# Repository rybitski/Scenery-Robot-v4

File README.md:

# SceneryRobotV4
Version 4 of the UVA Stage Robotics Development Project

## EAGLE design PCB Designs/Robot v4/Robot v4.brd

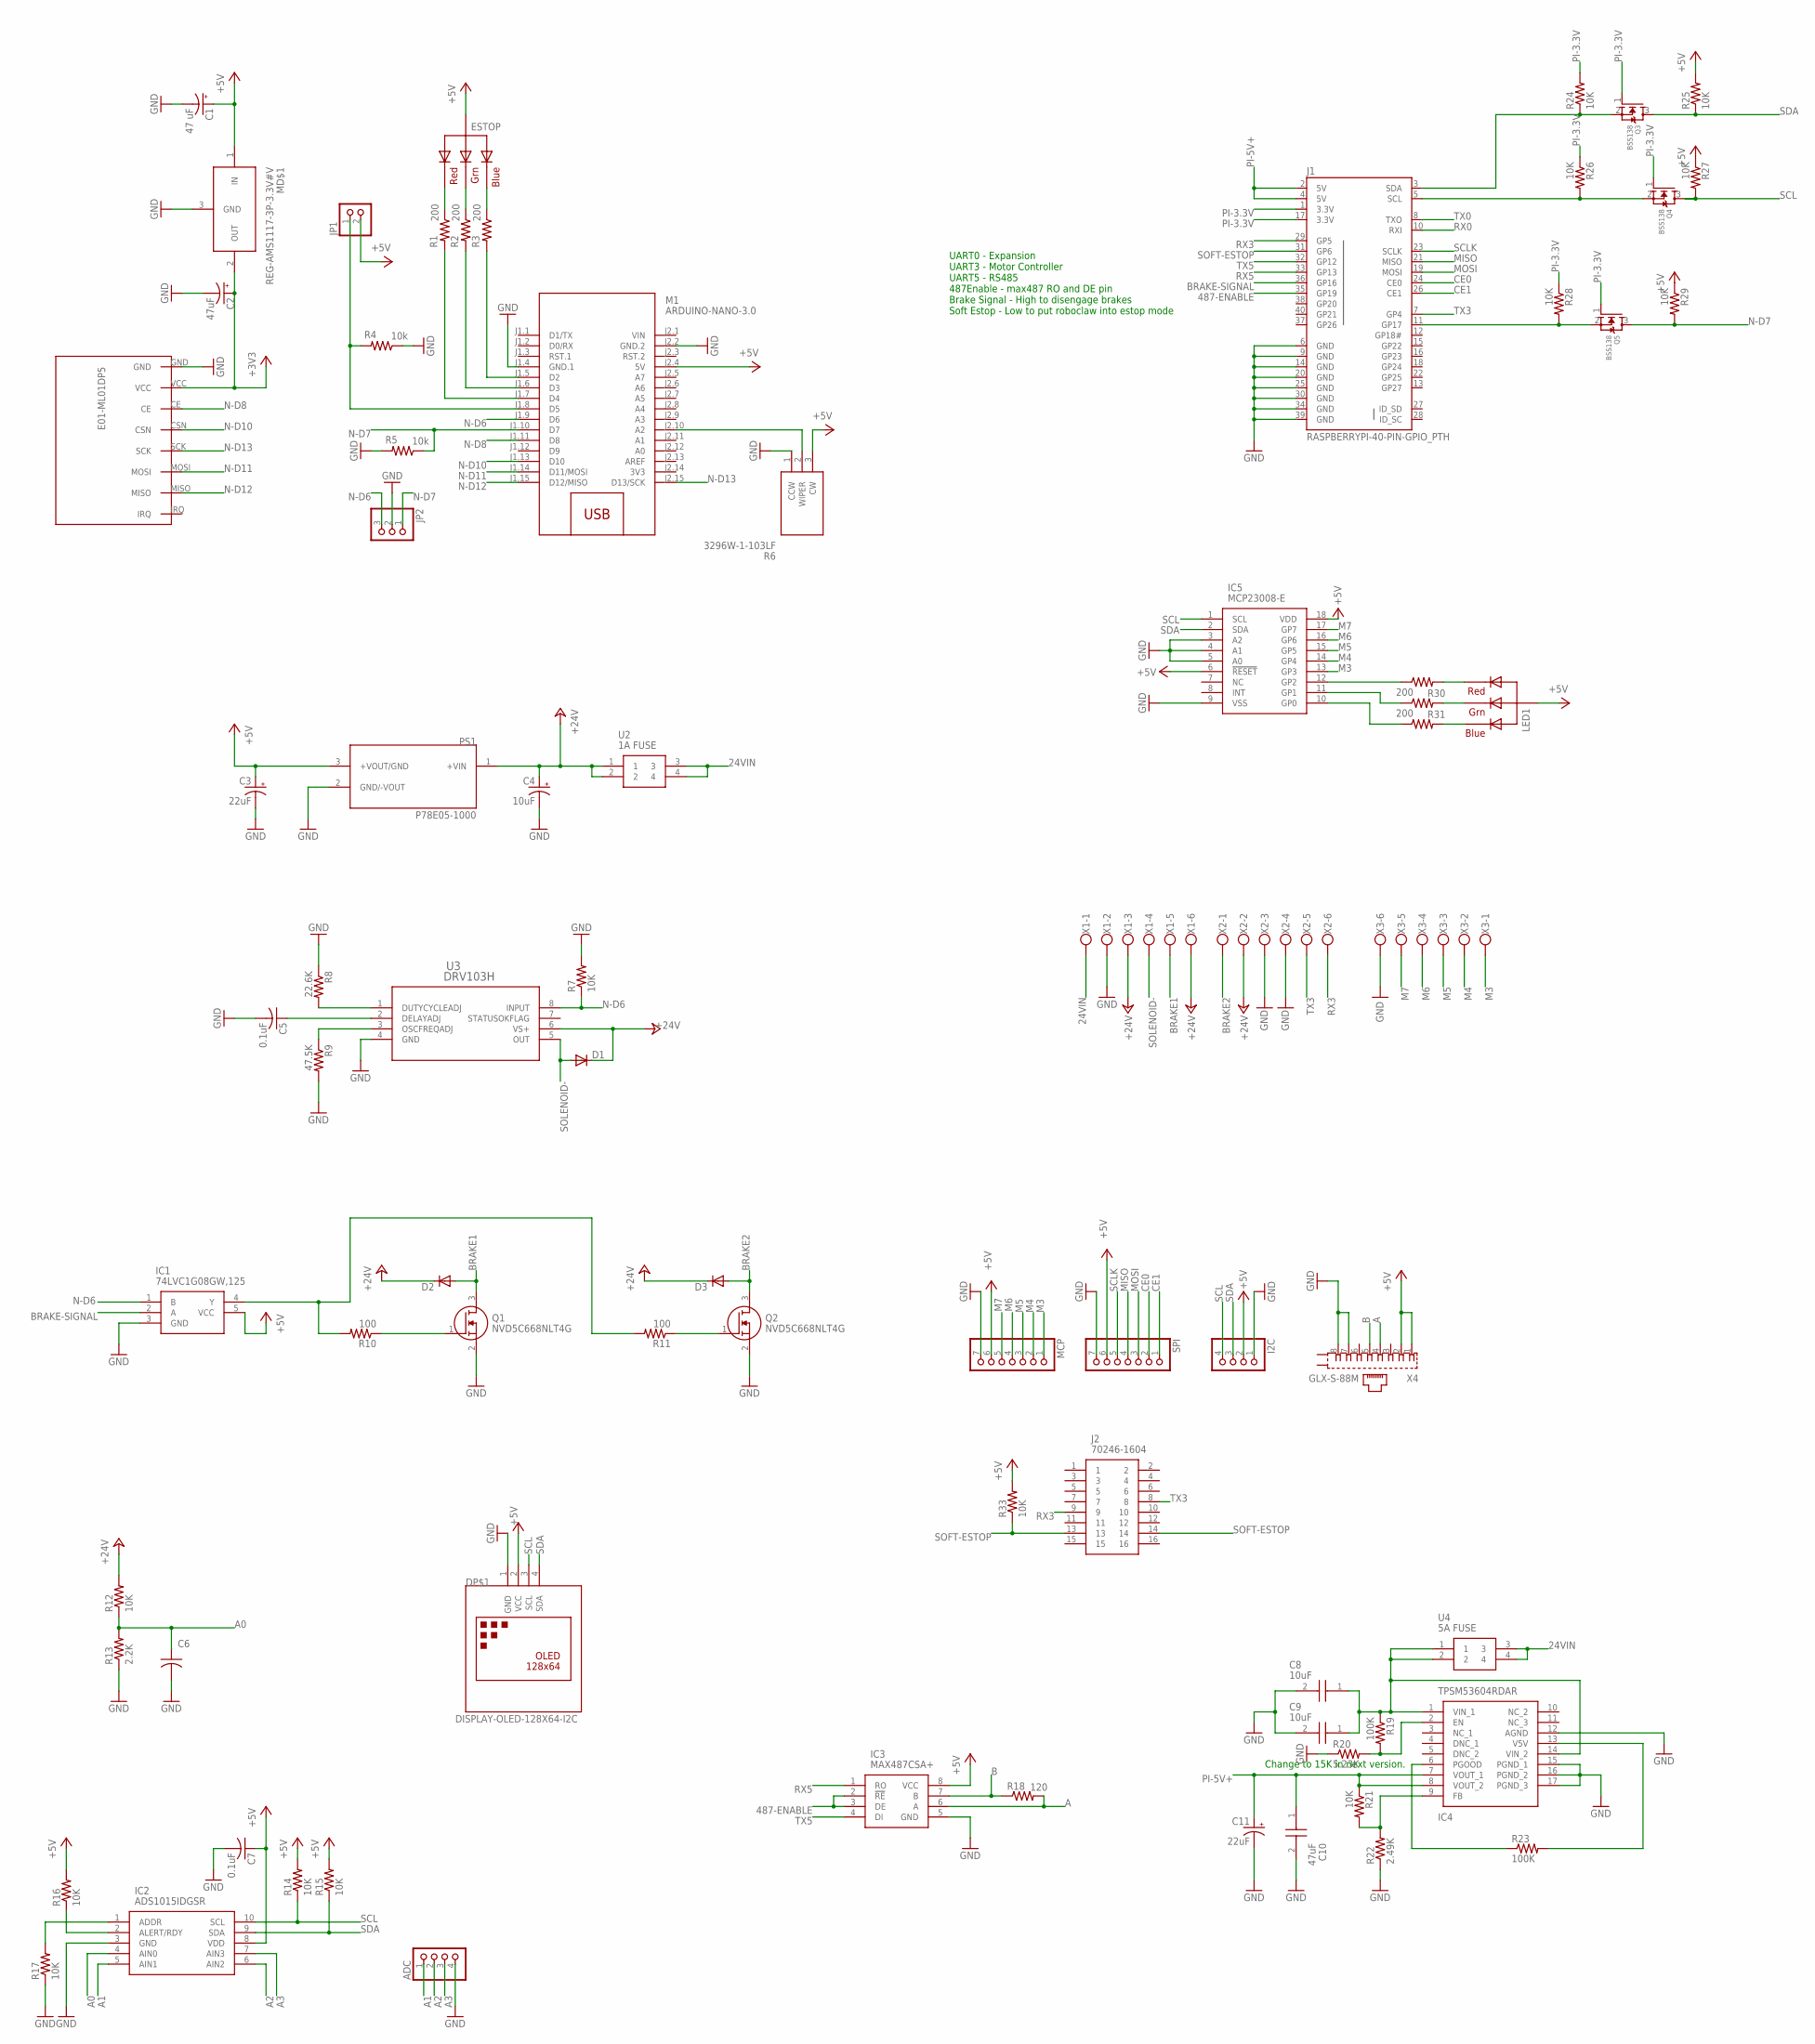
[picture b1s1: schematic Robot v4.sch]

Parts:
ADC: PINHD-1X4; 1X04
C1: 47 uF; E2,5-5
C2: 47uF; E2,5-5
C3, C11: 22uF; E3,5-8
C4: 10uF; E3,5-8
C5, C7: 0.1uF; C0805
C6: 0.01uF; C0805
C8, C9: 10uF; CAPC3216X180N
C10: 47uF; CAPC2012X145N
D1, D2, D3: DIODESOD-123; SOD-123
DP$1: DISPLAY-OLED-128X64-I2C
ESTOP: RGBLED_CA-5MM; LED5MMRGB
I2C: PINHD-1X4; 1X04
IC1: 74LVC1G08GW,125; SOT65P212X110-5N
IC2: ADS1015IDGSR; SOP50P490X110-10N
IC3: MAX487CSA+; SOIC127P600X175-8N
IC4: TPSM53604RDAR
IC5: MCP23008-E; SOIC127P1030X265-18N
J1: RASPBERRYPI-40-PIN-GPIO_PTH; 2X20_SHROUDED
J2: 70246-1604; SHDR16W64P254_2X8_2794X889X947
JP1: PINHD-1X2; 1X02
JP2: PINHD-1X3; 1X03
LED1: RGBLED_CA-5MM; LED5MMRGB
M1: ARDUINO-NANO-3.0
MCP: PINHD-1X7; 1X07
MD$1: REG-AMS1117-3P-3.3V#V; REG-AMS1117-3P#V
MD$2: E01-ML01DP5
PS1: P78E05-1000; CONV_P78E05-1000
Q1, Q2: NVD5C668NLT4G; DPAK_(SINGLE-GAUGE)_TO-252(369
Q3, Q4, Q5: BSS138; SOT23
R1, R2, R3, R30, R31, R32: 200; M0805
R4, R5: 10k; M0805
R6: 3296W-1-103LF; SHDR3W54P0X254_1X3_953X483X115
R7, R12: 10K; M0805
R8: 22.6K; M0805
R9: 47.5K; M0805
R10, R11: 100; M0805
R13: 2.2K; M0805
R14, R15, R16, R17, R21, R24, R25, R26, R27, R28, R29, R33: 10K; R0805
R18: 120; R0805
R19, R23: 100K; R0805
R20: 5.23K; R0805
R22: 2.49K; R0805
SPI: PINHD-1X7; 1X07
U2: 1A FUSE; 3568
U3: DRV103H; DDA8
U4: 5A FUSE; 3568
X1, X2, X3: W237-136
X4: GLX-S-88M

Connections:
3V3: M1.J2.14 (3V3)
24VIN: U2.3, U2.4, U4.3, U4.4, X1.1
487-ENABLE: IC3.2 (!RE), IC3.3 (DE), J1.35 (GP19)
+3V3: C2.+, MD$1.2 (OUT), MD$2.VCC
+5V: C1.+, C3.+, C7.1, DP$1.2 (VCC), ESTOP.2 (VCC), I2C.2, IC1.5 (VCC), IC2.8 (VDD), IC3.8 (VCC), IC5.6 (!RESET), IC5.18 (VDD), JP1.2, LED1.2 (VCC), M1.J2.4 (5V), MCP.6, MD$1.1 (IN), PS1.3 (+VOUT/GND), R6.3 (CW), R14.2, R15.2, R16.2, R25.2, R27.1, R29.1, R33.2, SPI.6, X4.1, X4.2
+24V: C4.+, D1.C, D2.C, D3.C, PS1.1 (+VIN), R12.2, U2.1, U2.2, U3.6 (VS+), X1.3, X1.6, X2.2
A: IC3.6 (A), R18.2, X4.4
A0: C6.1, IC2.4 (AIN0), R12.1, R13.2
A1: ADC.1, IC2.5 (AIN1)
A2: ADC.2, IC2.6 (AIN2)
A3: ADC.3, IC2.7 (AIN3)
B: IC3.7 (B), R18.1, X4.5
BRAKE1: D2.A, Q1.3 (D), X1.5
BRAKE2: D3.A, Q2.3 (D), X2.1
BRAKE-SIGNAL: IC1.2 (A), J1.36 (GP16)
CE0: J1.24 (CE0), SPI.2
CE1: J1.26 (CE1), SPI.1
GND: ADC.4, C1.-, C2.-, C3.-, C4.-, C5.2, C6.2, C7.2, C8.2, C9.2, C10.2, C11.-, DP$1.1 (GND), I2C.1, IC1.3 (GND), IC2.3 (GND), IC3.5 (GND), IC4.12 (AGND), IC4.15 (PGND_1), IC4.16 (PGND_2), IC4.17 (PGND_3), IC5.3 (A2), IC5.4 (A1), IC5.5 (A0), IC5.9 (VSS), J1.6 (GND), J1.9 (GND), J1.14 (GND), J1.20 (GND), J1.25 (GND), J1.30 (GND), J1.34 (GND), J1.39 (GND), JP2.2, M1.J1.4 (GND.1), M1.J2.2 (GND.2), MCP.7, MD$1.3 (GND), MD$2.GND, PS1.2 (GND/-VOUT), Q1.2 (S), Q2.2 (S), R4.1, R5.2, R6.1 (CCW), R7.2, R8.1, R9.2, R13.1, R17.1, R20.1, R22.1, SPI.7, U3.4 (GND), X1.2, X2.3, X2.4, X3.6, X4.7, X4.8
M3: IC5.13 (GP3), MCP.1, X3.1
M4: IC5.14 (GP4), MCP.2, X3.2
M5: IC5.15 (GP5), MCP.3, X3.3
M6: IC5.16 (GP6), MCP.4, X3.4
M7: IC5.17 (GP7), MCP.5, X3.5
MISO: J1.21 (MISO), SPI.4
MOSI: J1.19 (MOSI), SPI.3
unnamed: IC5.12 (GP2), R30.1
unnamed: IC5.11 (GP1), R31.1
unnamed: C8.1, C9.1, IC4.1 (VIN_1), IC4.14 (VIN_2), R19.1, U4.1, U4.2
unnamed: IC1.4 (Y), R10.2, R11.2
unnamed: J1.5 (SCL), Q4.2 (S), R26.2
unnamed: Q2.1 (G), R11.1
unnamed: Q1.1 (G), R10.1
unnamed: J1.3 (SDA), Q3.2 (S), R24.1
unnamed: IC5.10 (GP0), R32.1
unnamed: IC4.2 (EN), R19.2, R20.2
unnamed: IC4.9 (FB), R21.2, R22.2
unnamed: J1.11 (GP17), Q5.2 (S), R28.2
unnamed: IC4.13 (V5V), R23.2
unnamed: IC4.6 (PGOOD), R23.1
unnamed: IC2.2 (ALERT/RDY), R16.1
unnamed: IC2.1 (ADDR), R17.2
unnamed: LED1.1 (RED), R30.2
unnamed: LED1.3 (GREEN), R31.2
unnamed: LED1.4 (BLUE), R32.2
unnamed: ESTOP.4 (BLUE), R3.1
unnamed: ESTOP.3 (GREEN), R2.1
unnamed: ESTOP.1 (RED), R1.1
unnamed: M1.J1.5 (D2), R3.2
unnamed: JP1.1, M1.J1.8 (D5), R4.2
unnamed: M1.J1.6 (D3), R2.2
unnamed: M1.J1.7 (D4), R1.2
unnamed: M1.J2.10 (A2), R6.2 (WIPER)
unnamed: C5.1, U3.2 (DELAYADJ)
unnamed: R9.1, U3.3 (OSCFREQADJ)
unnamed: R8.2, U3.1 (DUTYCYCLEADJ)
N-D6: IC1.1 (B), JP2.3, M1.J1.9 (D6), R7.1, U3.8 (INPUT)
N-D7: JP2.1, M1.J1.10 (D7), Q5.3 (D), R5.1, R29.2
N-D8: M1.J1.11 (D8), MD$2.CE
N-D10: M1.J1.13 (D10), MD$2.CSN
N-D11: M1.J1.14 (D11/MOSI), MD$2.MOSI
N-D12: M1.J1.15 (D12/MISO), MD$2.MISO
N-D13: M1.J2.15 (D13/SCK), MD$2.SCK
PI-3.3V: J1.1 (3.3V), J1.17 (3.3V), Q3.1 (G), Q4.1 (G), Q5.1 (G), R24.2, R26.1, R28.1
PI-5V+: C10.1, C11.+, IC4.7 (VOUT_1), IC4.8 (VOUT_2), J1.2 (5V), J1.4 (5V), R21.1
RX0: J1.10 (RXI)
RX3: J1.29 (GP5), J2.9, X2.6
RX5: IC3.1 (RO), J1.33 (GP13)
SCL: DP$1.3 (SCL), I2C.4, IC2.10 (SCL), IC5.1 (SCL), Q4.3 (D), R14.1, R27.2
SCLK: J1.23 (SCLK), SPI.5
SDA: DP$1.4 (SDA), I2C.3, IC2.9 (SDA), IC5.2 (SDA), Q3.3 (D), R15.1, R25.1
SOFT-ESTOP: J1.31 (GP6), J2.13, J2.14, R33.1
SOLENOID-: D1.A, U3.5 (OUT), X1.4
TX0: J1.8 (TXO)
TX3: J1.7 (GP4), J2.8, X2.5
TX5: IC3.4 (DI), J1.32 (GP12)
VIN: M1.J2.1 (VIN)

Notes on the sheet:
UART0 - Expansion UART3 - Motor Controller UART5 - RS485 487Enable - max487 RO and DE pin Brake Signal - High to disengage brakes Soft Estop - Low to put roboclaw into estop mode
Change to 15K in next version.

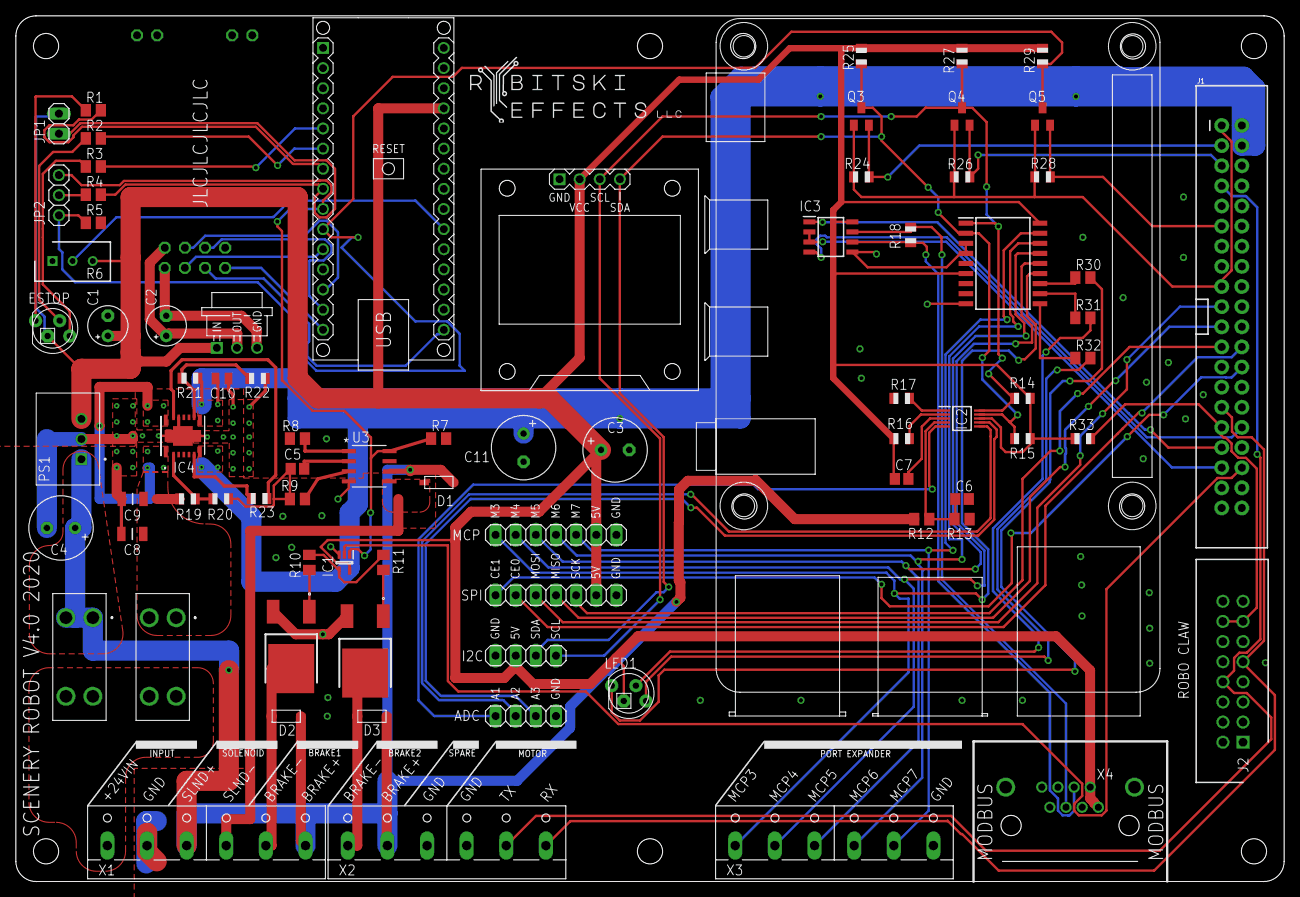
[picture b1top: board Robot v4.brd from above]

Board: 2 copper layers, 160.0 x 109.2 mm, 79 parts (0 on the bottom side), 72 nets.

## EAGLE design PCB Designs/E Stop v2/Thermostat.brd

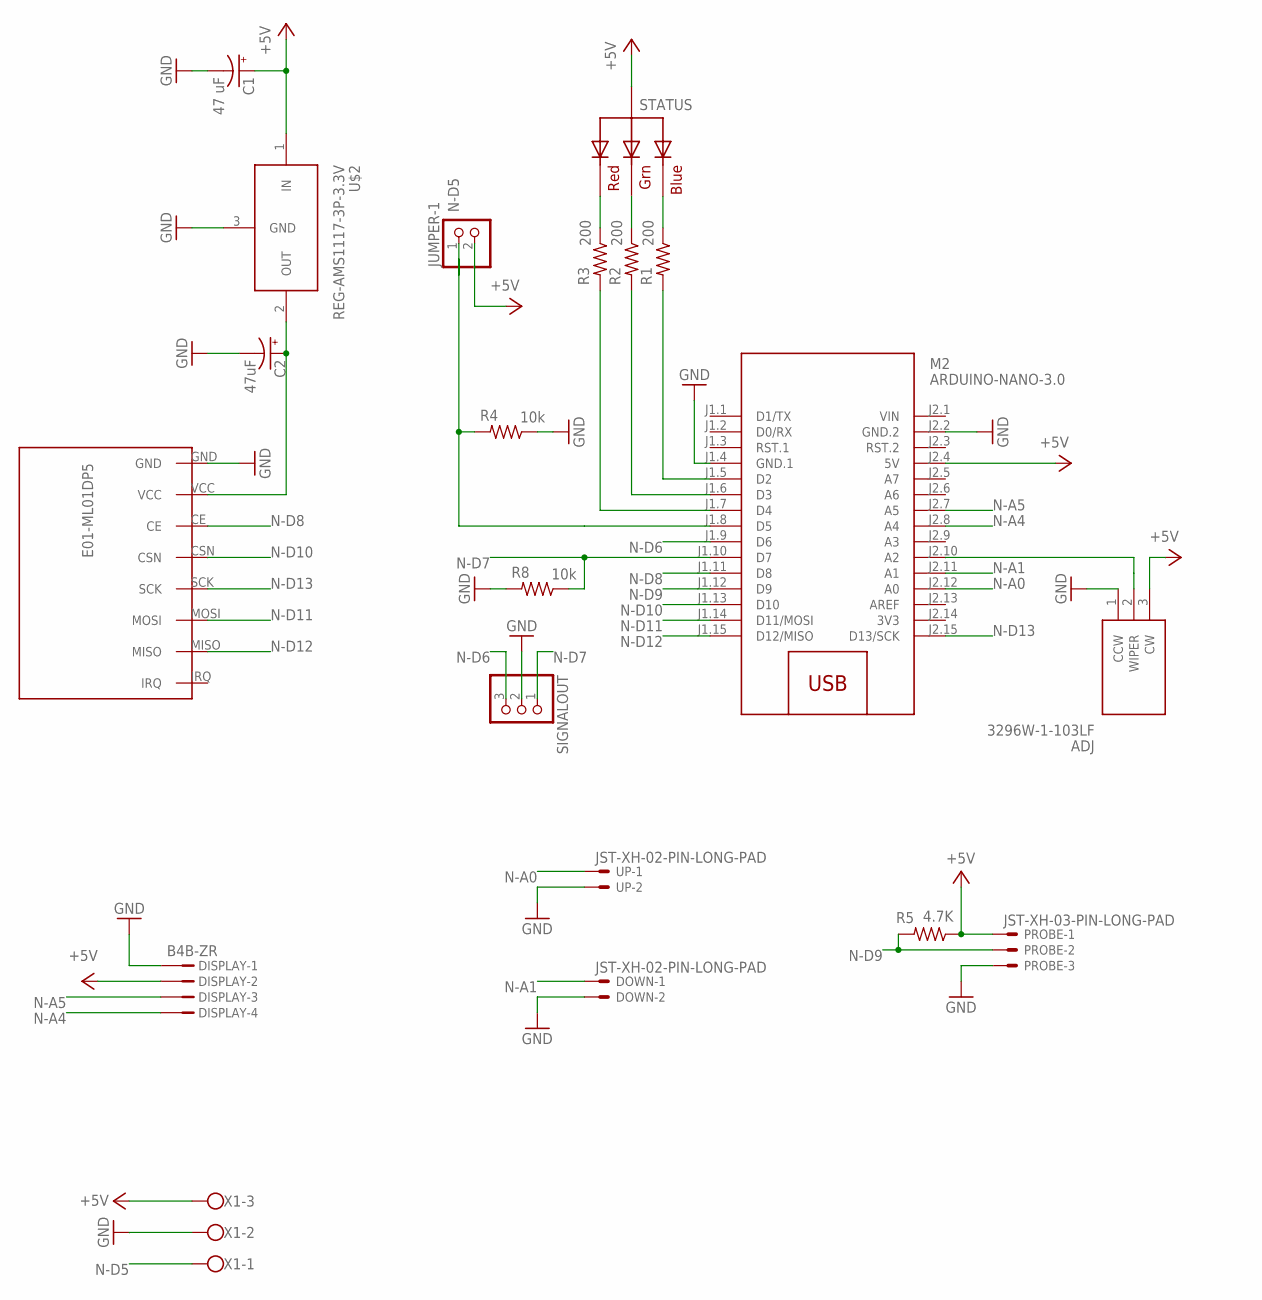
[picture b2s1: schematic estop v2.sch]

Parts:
ADJ: 3296W-1-103LF; SHDR3W54P0X254_1X3_953X483X115
C1: 47 uF; E2,5-5
C2: 47uF; E2,5-5
DISPLAY: B4B-ZR
DOWN: JST-XH-02-PIN-LONG-PAD; JST-XH-02-PACKAGE-LONG-PAD
JUMPER-1: PINHD-1X2; 1X02
M2: ARDUINO-NANO-3.0
PROBE: JST-XH-03-PIN-LONG-PAD; JST-XH-03-PACKAGE-LONG-PAD
R1, R2, R3: 200; M0805
R4, R8: 10k; M0805
R5: 4.7K; M0805
SIGNALOUT: PINHD-1X3; 1X03
STATUS: RGBLED_CA-5MM; LED5MMRGB
U$1: E01-ML01DP5
U$2: REG-AMS1117-3P-3.3V; REG-AMS1117-3P
UP: JST-XH-02-PIN-LONG-PAD; JST-XH-02-PACKAGE-LONG-PAD
X1: W237-103

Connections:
3V3: M2.J2.14 (3V3)
+5V: ADJ.3 (CW), C1.+, DISPLAY.2, JUMPER-1.2, M2.J2.4 (5V), PROBE.1, R5.1, STATUS.2 (VCC), U$2.1 (IN), X1.3
GND: ADJ.1 (CCW), C1.-, C2.-, DISPLAY.1, DOWN.2, M2.J1.4 (GND.1), M2.J2.2 (GND.2), PROBE.3, R4.1, R8.2, SIGNALOUT.2, U$1.GND, U$2.3 (GND), UP.2, X1.2
unnamed: M2.J1.6 (D3), R2.2
unnamed: C2.+, U$1.VCC, U$2.2 (OUT)
unnamed: R1.1, STATUS.4 (BLUE)
unnamed: R2.1, STATUS.3 (GREEN)
unnamed: R3.1, STATUS.1 (RED)
unnamed: M2.J1.5 (D2), R1.2
unnamed: M2.J1.7 (D4), R3.2
unnamed: ADJ.2 (WIPER), M2.J2.10 (A2)
N-A0: M2.J2.12 (A0), UP.1
N-A1: DOWN.1, M2.J2.11 (A1)
N-A4: DISPLAY.4, M2.J2.8 (A4)
N-A5: DISPLAY.3, M2.J2.7 (A5)
N-D5: JUMPER-1.1, M2.J1.8 (D5), R4.2, X1.1
N-D6: M2.J1.9 (D6), SIGNALOUT.3
N-D7: M2.J1.10 (D7), R8.1, SIGNALOUT.1
N-D8: M2.J1.11 (D8), U$1.CE
N-D9: M2.J1.12 (D9), PROBE.2, R5.2
N-D10: M2.J1.13 (D10), U$1.CSN
N-D11: M2.J1.14 (D11/MOSI), U$1.MOSI
N-D12: M2.J1.15 (D12/MISO), U$1.MISO
N-D13: M2.J2.15 (D13/SCK), U$1.SCK
VIN: M2.J2.1 (VIN)

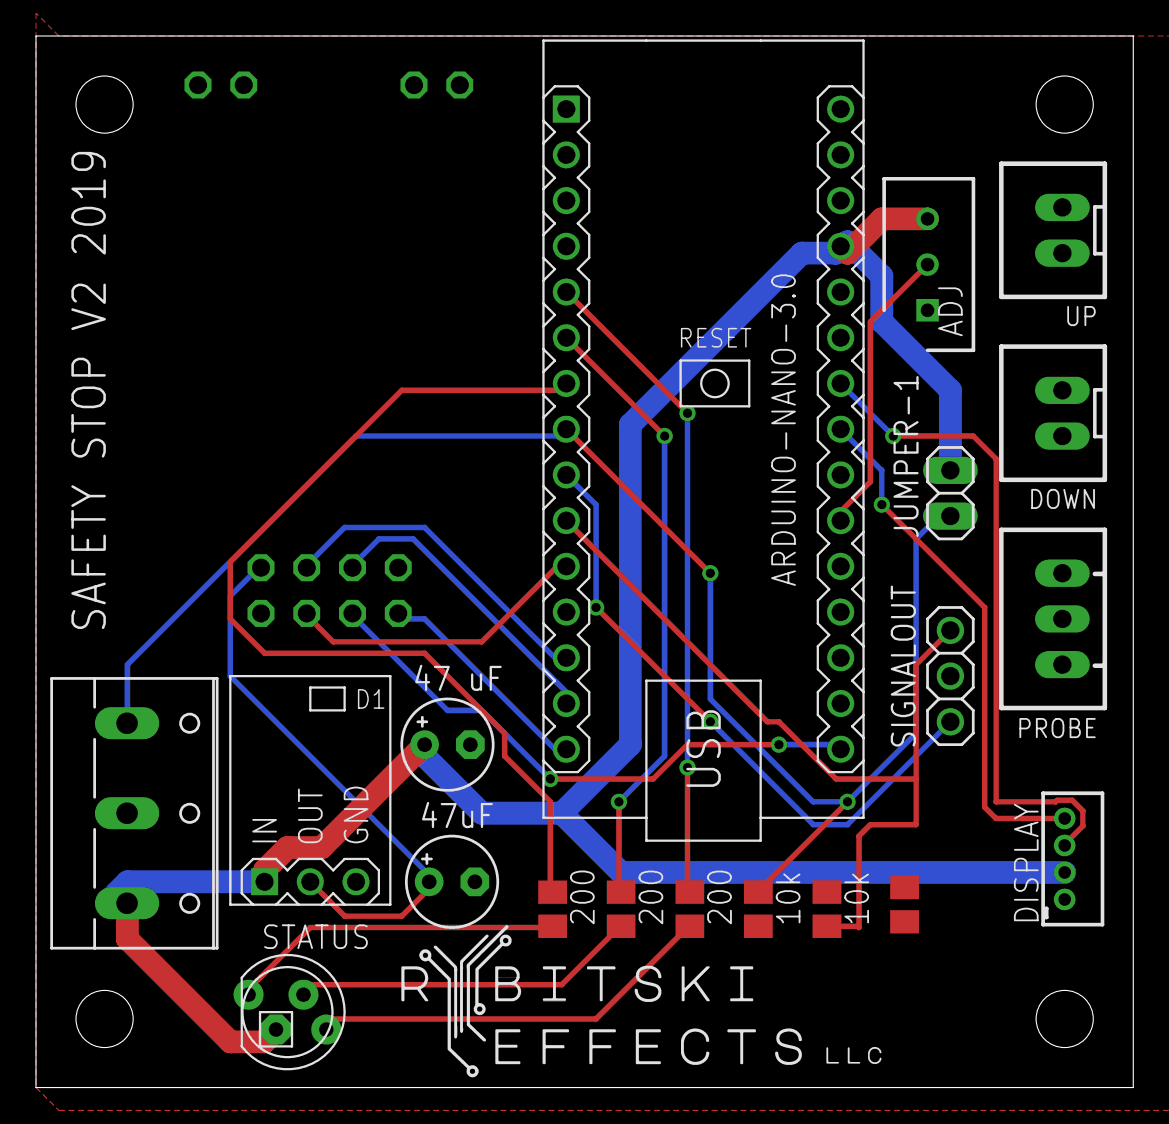
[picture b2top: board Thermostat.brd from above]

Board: 2 copper layers, 61.0 x 58.4 mm, 20 parts (0 on the bottom side), 23 nets.

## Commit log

2021-02-11 Removed unused files
2021-02-25 Uploaded new files, updated RobotMovement
2021-03-18 added version 1 of website
2021-03-25 Newest robot movement code
2021-03-31 Robot Spline Tracking appears to be working
2021-04-08 Attempt to fix end and start being the same
2021-04-22 Fixed Robot path overlap issues
2021-04-27 Version 2 of the Website
2021-04-30 Added back end NodeJs server
2021-04-30 changed test server to input
2021-05-03 Changed Version 2 to Version2
2021-05-04 pair matched X & Y axis
2021-05-04 changes to splinedraw
2021-09-17 fixed upload workspace point editing
2021-09-21 upload workspace changes
2021-09-30 Added Safety Stop Code
2021-09-30 Added PCB Files
2021-09-30 Removed extra files, change folder name
2021-10-03 Version 3 Dark Mode and UI change
2021-10-06 fun stuff
2021-10-08 removed version 3
2021-10-08 added version 3 read me file
2021-10-08 added version 3
2021-10-13 updated the drawing panel
2021-10-26 added reverse command to Robot Movement
2021-11-03 added B-Spline curve, need to modify the weights in the python file
2021-11-05 added corrected upload and save feature
2021-11-09 mergeee
2021-11-09 tinkering
2021-11-17 fixed macos problem w/ b-spline (dynamic path based on OS)
2021-11-17 grid state fix
2021-11-23 added panel for robot communication and fixed python file for robot movement
2021-11-23 work in progress
2021-11-24 stashing changes
2021-11-25 temp changes
2021-11-27 landing page html/css
2021-11-27 separated landing and tutorial pages
2021-11-27 link github icon
2021-11-27 changed id names to match pictures
2021-11-29 cue system on upload working
2021-11-29 fixed switch back to full path
2021-11-29 fixed highlighting weight inconsistencies
2021-11-30 save cues working
2021-11-30 start split cue
2021-11-30 Finalized start position functionality, removed draw rate slider and replaced with constant value of 0.01
2021-11-30 add faq page
2021-11-30 update title, clear documentation page
2021-11-30 clear documentation page
2021-12-03 Fixed y-axis start rectangle placement
2021-12-03 robot code
2021-12-07 working cue view and robot communications
2021-12-07 puts option on app.js
2021-12-07 fixed html
2021-12-09 Implement Ground Plan viewer
2021-12-09 Add .gitignore
2021-12-09 File server change
2021-12-12 idek:
2021-12-12 get basic button/pictures of tutorial
2021-12-13 Enable ground plan visibility toggling
2021-12-13 fixed b-spline
2021-12-13 added library for icons in the right panel
2021-12-13 added package for xlsx file saving so no longer need url
2021-12-13 updated faq answers
2021-12-13 Revert "Change sample text for FAQ 1-3"
2022-03-04 up to date
2022-03-04 dsstore
2022-03-04 no DS_Store
2022-03-04 fixed HTML icon
2022-03-04 pls just work man

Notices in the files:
parts and their libraries:
diy-modules: Released under the Creative Commons Attribution 4.0 International License: http://creativecommons.org/licenses/by/4.0
SparkFun-Connectors: Licensing: Creative Commons ShareAlike 4.0 International - https://creativecommons.org/licenses/by-sa/4.0
